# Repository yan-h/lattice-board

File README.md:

MIDI controller using the Wicki-Hayden layout. Heavily inspired by [Hexboard](https://shapingthesilence.com/tech/hexboard-midi-controller/), [Striso](https://www.striso.org) and [Lumatone](https://www.lumatone.io).
- 123 keys with individual LED lighting
  - 5 octaves
  - Fifthspan of 25 - i.e. each octave contains 25 notes, spanning an unbroken segment of the chain of fifths
    - Size of fifth is adjustable in firmware, providing easy access to all temperaments based on pure octaves and a chain of equal-sized perfect fifths.
- Very portable
  - 21x22x2.5cm
  - Similar in size to a small tablet, and much lighter than one.
- Tiny keys (17mm) for my tiny hands (and easier microtonal chords)
- No velocity sensitivity (or any other form of MIDI expression). This simplifies the engineering constraints by a lot, and let me design it as a very weirdly shaped mechanical keyboard.

Engineering overview
- Case and keycaps 3D-printed in PETG (Bambu Lab translucent PETG and black PETG-HF)
  - [3D models](https://cad.onshape.com/documents?nodeId=e71b068a262a341693bc0b63&resourceType=folder) made using Onshape. 
  - Printed using a Bambu Lab P1S. Keycaps were printed with the Darkmoon Satin build plate, to obtain a texture finer than a textured PEI plate, but coarser than a smooth plate.
- TTC Frozen Silent V2 Keyswitches - fully transparent, light condenser, silent.
- PCB designed in KiCad 9, manufactured with JLCPCB
- Firmware in Rust with [Embassy](https://embassy.dev/). Heavily vibecoded.
  - See [firmware/README.md](firmware/README.md) for build and flashing instructions, and the serial configuration dashboard.

Future work: [7-octave, fifthspan-50 redesign findings](docs/7x50-redesign-notes.md).

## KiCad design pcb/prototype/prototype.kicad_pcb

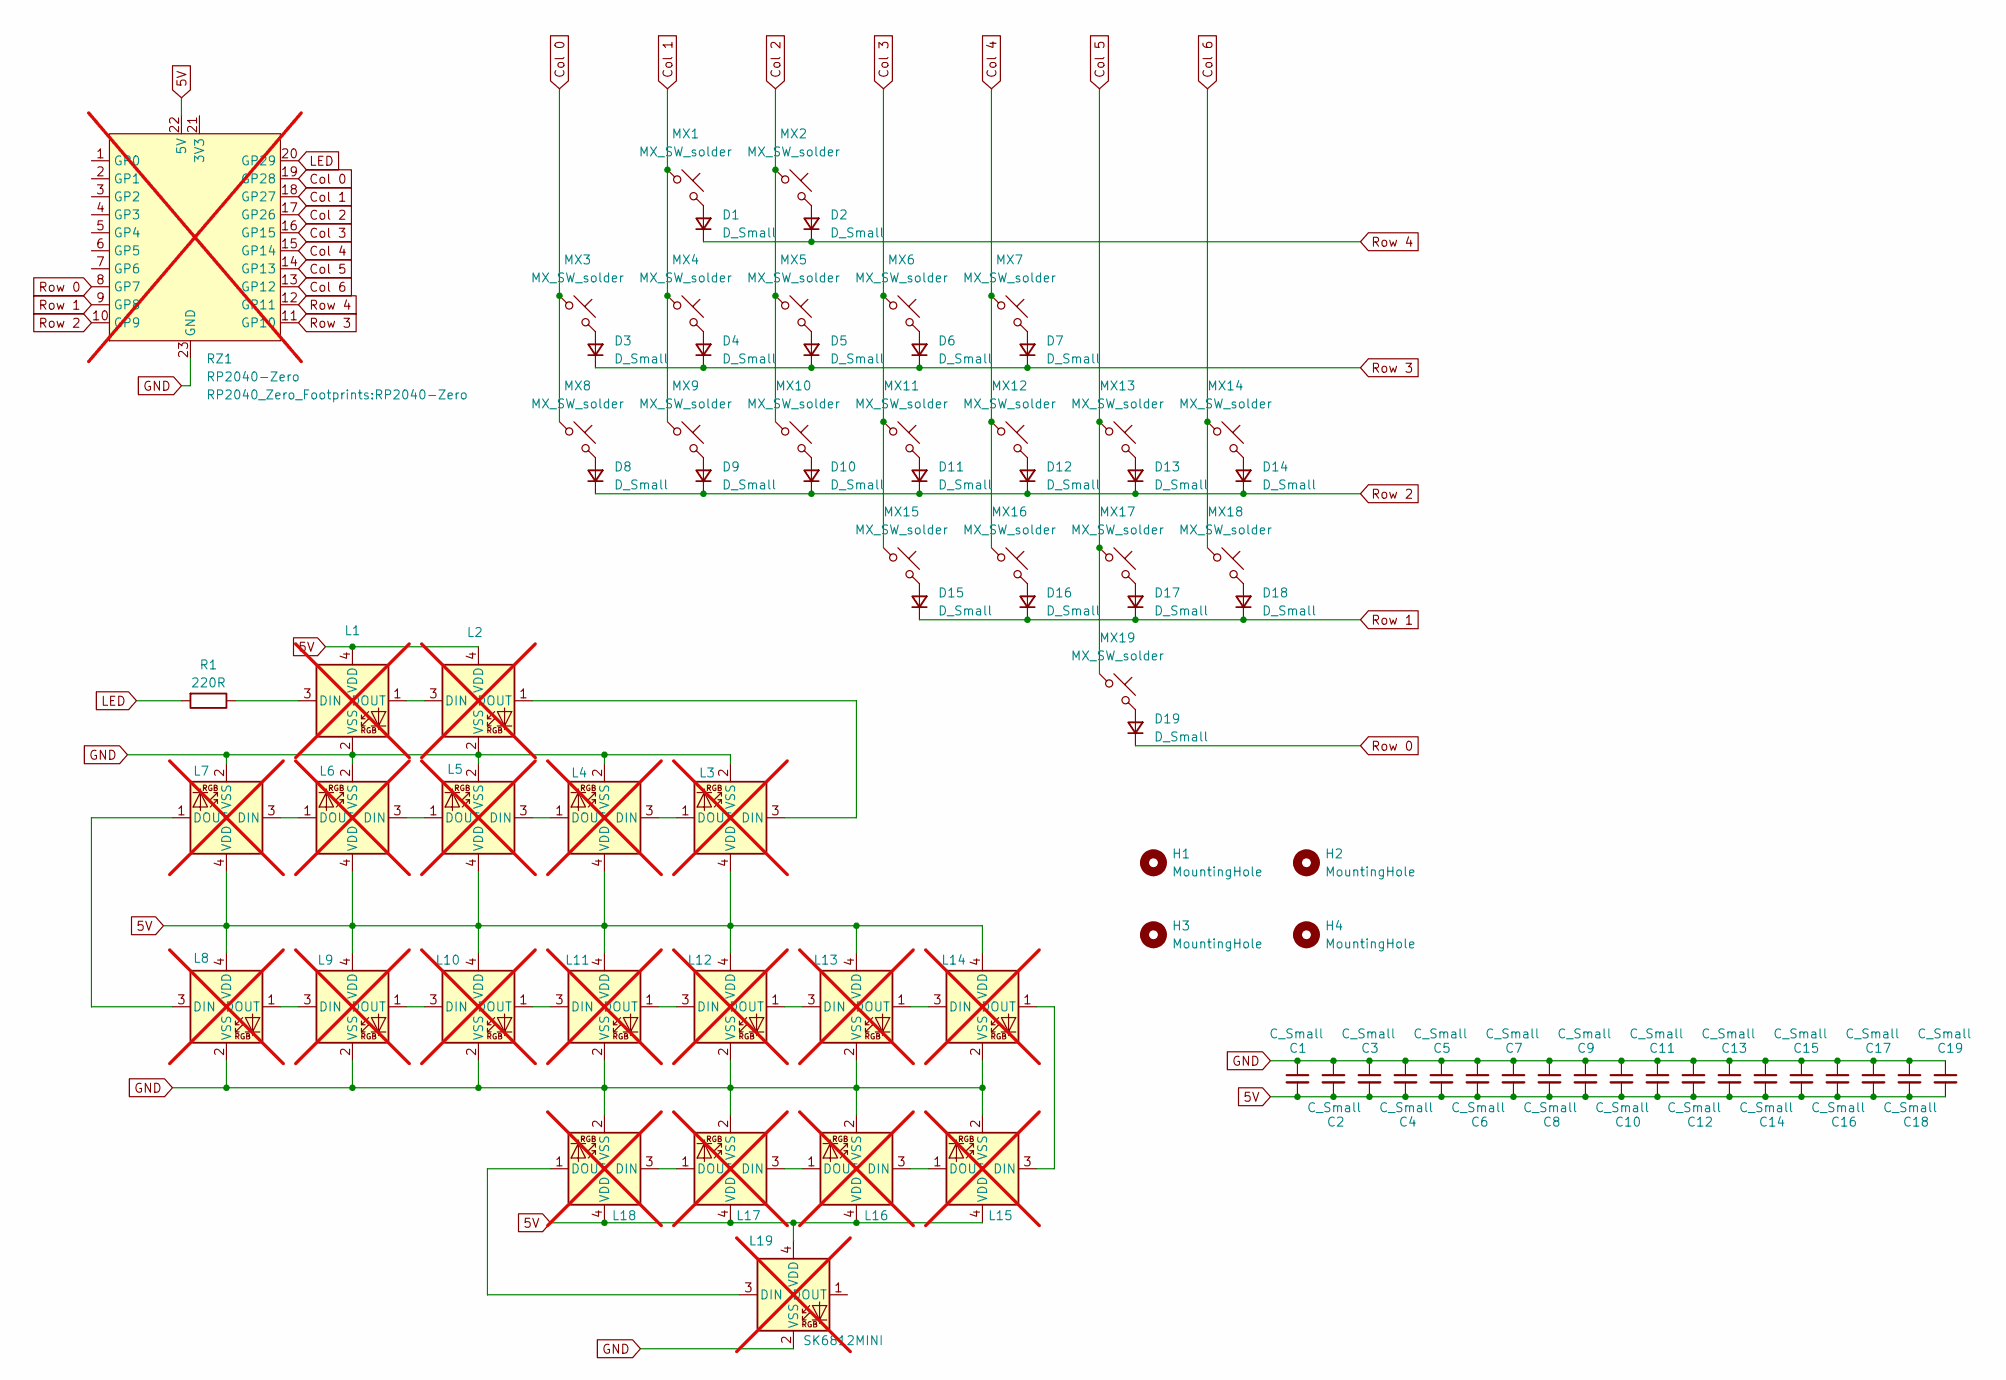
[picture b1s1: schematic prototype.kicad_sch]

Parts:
C1, C2, C3, C4, C5, C6, C7, C8, C9, C10, C11, C12, C13, C14, C15, C16, C17, C18, C19: C_Small; C_0603_1608Metric
D1, D2, D3, D4, D5, D6, D7, D8, D9, D10, D11, D12, D13, D14, D15, D16, D17, D18, D19: D_Small; D_SOD-323F
H1, H2, H3, H4: MountingHole; MountingHole_2.2mm_M2_Pad
L1, L2, L3, L4, L5, L6, L7, L8, L9, L10, L11, L12, L13, L14, L15, L16, L17, L18, L19: SK6812MINI; SK6812-MINI-E; not fitted
MX1, MX2, MX3, MX4, MX5, MX6, MX7, MX8, MX9, MX10, MX11, MX12, MX13, MX14, MX15, MX16, MX17, MX18, MX19: MX_SW_solder; SW_MX_16
R1: 220R; R_0402_1005Metric
RZ1: RP2040-Zero; not fitted

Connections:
5V: C1.2, C2.2, C3.2, C4.2, C5.2, C6.2, C7.2, C8.2, C9.2, C10.2, C11.2, C12.2, C13.2, C14.2, C15.2, C16.2, C17.2, C18.2, C19.2, L1.4 (VDD), L2.4 (VDD), L3.4 (VDD), L4.4 (VDD), L5.4 (VDD), L6.4 (VDD), L7.4 (VDD), L8.4 (VDD), L9.4 (VDD), L10.4 (VDD), L11.4 (VDD), L12.4 (VDD), L13.4 (VDD), L14.4 (VDD), L15.4 (VDD), L16.4 (VDD), L17.4 (VDD), L18.4 (VDD), L19.4 (VDD), RZ1.22 (5V)
Col 0: MX3.1, MX8.1, RZ1.19 (GP28)
Col 1: MX1.1, MX4.1, MX9.1, RZ1.18 (GP27)
Col 2: MX2.1, MX5.1, MX10.1, RZ1.17 (GP26)
Col 3: MX6.1, MX11.1, MX15.1, RZ1.16 (GP15)
Col 4: MX7.1, MX12.1, MX16.1, RZ1.15 (GP14)
Col 5: MX13.1, MX17.1, MX19.1, RZ1.14 (GP13)
Col 6: MX14.1, MX18.1, RZ1.13 (GP12)
GND: C1.1, C2.1, C3.1, C4.1, C5.1, C6.1, C7.1, C8.1, C9.1, C10.1, C11.1, C12.1, C13.1, C14.1, C15.1, C16.1, C17.1, C18.1, C19.1, L1.2 (VSS), L2.2 (VSS), L3.2 (VSS), L4.2 (VSS), L5.2 (VSS), L6.2 (VSS), L7.2 (VSS), L8.2 (VSS), L9.2 (VSS), L10.2 (VSS), L11.2 (VSS), L12.2 (VSS), L13.2 (VSS), L14.2 (VSS), L15.2 (VSS), L16.2 (VSS), L17.2 (VSS), L18.2 (VSS), L19.2 (VSS), RZ1.23 (GND)
LED: R1.2, RZ1.20 (GP29)
unnamed: D1.2 (A), MX1.2
unnamed: D2.2 (A), MX2.2
unnamed: D3.2 (A), MX3.2
unnamed: D4.2 (A), MX4.2
unnamed: D5.2 (A), MX5.2
unnamed: D6.2 (A), MX6.2
unnamed: D7.2 (A), MX7.2
unnamed: D8.2 (A), MX8.2
unnamed: D9.2 (A), MX9.2
unnamed: D10.2 (A), MX10.2
unnamed: D11.2 (A), MX11.2
unnamed: D12.2 (A), MX12.2
unnamed: D13.2 (A), MX13.2
unnamed: D14.2 (A), MX14.2
unnamed: D15.2 (A), MX15.2
unnamed: D16.2 (A), MX16.2
unnamed: D17.2 (A), MX17.2
unnamed: D18.2 (A), MX18.2
unnamed: D19.2 (A), MX19.2
unnamed: L1.3 (DIN), R1.1
unnamed: L1.1 (DOUT), L2.3 (DIN)
unnamed: L2.1 (DOUT), L3.3 (DIN)
unnamed: L3.1 (DOUT), L4.3 (DIN)
unnamed: L4.1 (DOUT), L5.3 (DIN)
unnamed: L5.1 (DOUT), L6.3 (DIN)
unnamed: L6.1 (DOUT), L7.3 (DIN)
unnamed: L7.1 (DOUT), L8.3 (DIN)
unnamed: L8.1 (DOUT), L9.3 (DIN)
unnamed: L9.1 (DOUT), L10.3 (DIN)
unnamed: L10.1 (DOUT), L11.3 (DIN)
unnamed: L11.1 (DOUT), L12.3 (DIN)
unnamed: L12.1 (DOUT), L13.3 (DIN)
unnamed: L13.1 (DOUT), L14.3 (DIN)
unnamed: L14.1 (DOUT), L15.3 (DIN)
unnamed: L15.1 (DOUT), L16.3 (DIN)
unnamed: L16.1 (DOUT), L17.3 (DIN)
unnamed: L17.1 (DOUT), L18.3 (DIN)
unnamed: L18.1 (DOUT), L19.3 (DIN)
Row 0: D19.1 (K), RZ1.8 (GP7)
Row 1: D15.1 (K), D16.1 (K), D17.1 (K), D18.1 (K), RZ1.9 (GP8)
Row 2: D8.1 (K), D9.1 (K), D10.1 (K), D11.1 (K), D12.1 (K), D13.1 (K), D14.1 (K), RZ1.10 (GP9)
Row 3: D3.1 (K), D4.1 (K), D5.1 (K), D6.1 (K), D7.1 (K), RZ1.11 (GP10)
Row 4: D1.1 (K), D2.1 (K), RZ1.12 (GP11)

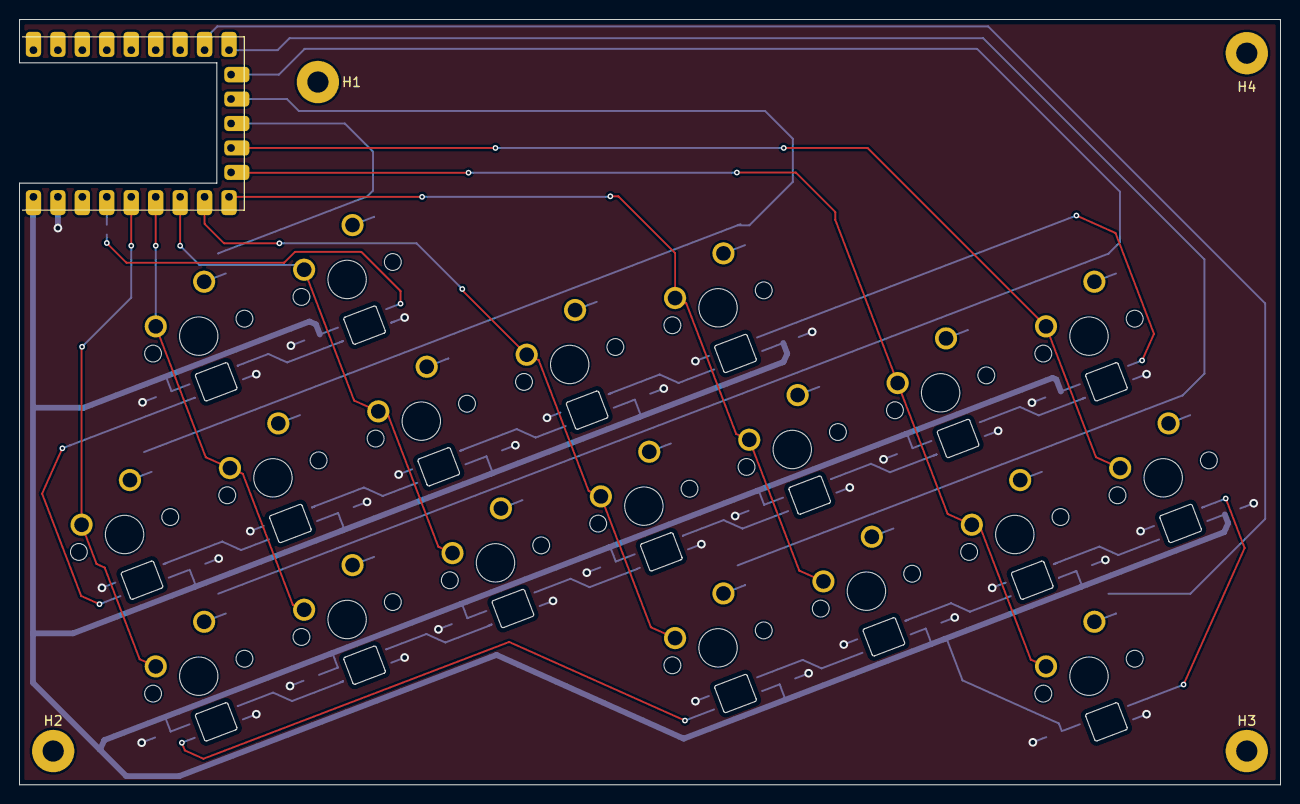
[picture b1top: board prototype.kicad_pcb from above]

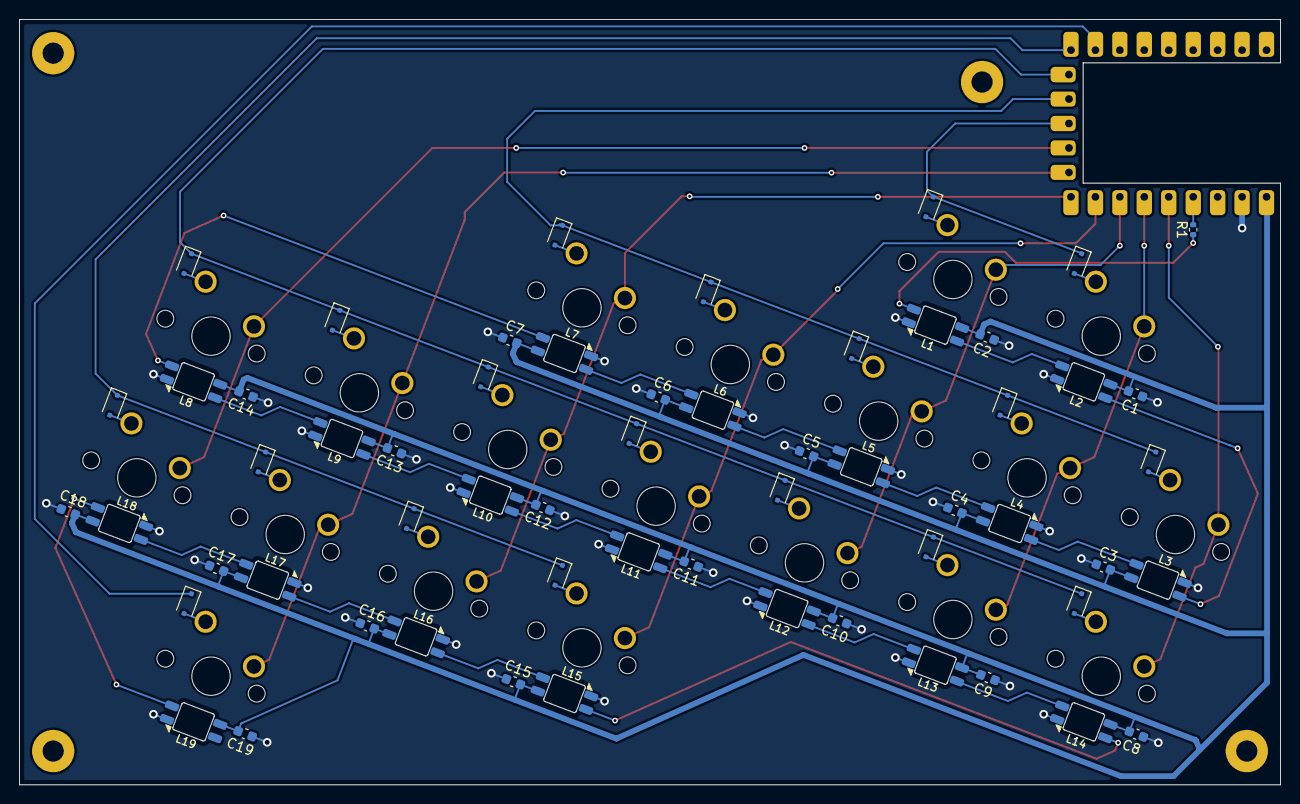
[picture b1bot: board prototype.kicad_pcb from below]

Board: 2 copper layers, 131.0 x 79.5 mm, 82 parts (58 on the bottom side), 53 nets.

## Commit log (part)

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2026-02-02 Add README
2026-02-05 Add MIT License to the project
2026-02-05 Update README with firmware details
    Added information about firmware written in Rust using Embassy.
2026-02-05 Fix link formatting for Embassy website in README
2026-02-16 Fix misshapen wall in models
2026-02-17 Update README with key size and sensitivity info
